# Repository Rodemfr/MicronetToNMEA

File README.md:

# MicronetToNMEA

## Note to Teensy users

MicronetToNMEA has migrated to ESP32. For Teensy-based hardware, please refer to the legacy code in the [`teensy`](https://github.com/Rodemfr/MicronetToNMEA/tree/teensy) branch.

## Description

MicronetToNMEA is an Arduino project that converts data from Raymarine's wireless Micronet network into standard NMEA0183 sentences, making it readily compatible with laptop or tablet navigation software. Additionally, it can transmit NMEA navigation data from your device back to the Micronet network.

Required hardware:
- A Raymarine/Tacktick master device (one with an ON/OFF button)
- An ESP32 WROOM DevKitC based board ([such as uPesy Wroom DevKit](https://www.upesy.fr/products/upesy-esp32-wroom-devkit-board))
- A CC1101 based board operating in the 868/915MHz range (ensure you order one with the appropriate 868MHz antenna, not the 433MHz one)

Optional components:
- A NMEA GPS/GNSS module connected via UART to provide position, time, date, SOG, and COG data to Micronet displays. The UBlox M8N is fully supported and can be configured directly by MicronetToNMEA
- A LSM303 compass module connected via I2C to provide magnetic heading data

Important Notice: While this DIY solution is an interesting project, please be aware that it may not withstand the harsh marine environment (salt, moisture, vibrations) as well as commercial equipment. MicronetToNMEA comes with no guarantees and should not be relied upon as your sole navigation system. For mission-critical applications, we recommend purchasing certified Raymarine/Tacktick equipment from authorized dealers.

## Authors & Contributors

* **Ronan Demoment** - [Rodemfr](https://github.com/Rodemfr) - Project creator and maintainer 
* **Dietmar Warning** - [dwarning](https://github.com/dwarning) - LSM303 Compass integration, bug fixes & testing
* **[j-lang](https://github.com/j-lang)** - UBLOX M8N initialization code & testing

## License

MicronetToNMEA is released under the GPLv3 license. See LICENSE.txt for complete details.

## Building the Project

The project can be built using [Visual Studio Code](https://code.visualstudio.com/) with the [PlatformIO](https://platformio.org/) extension installed.

For detailed instructions, please refer to the [User Manual](https://github.com/Rodemfr/MicronetToNMEA/blob/master/doc/user_manual/user_manual.md).

## Acknowledgments

* Special thanks to the YBW.com forum members who initiated the investigation of the Micronet protocol. Technical discussions can be found here: https://forums.ybw.com/index.php?threads/raymarines-micronet.539500/
* We appreciate all users who provide feedback and report issues, helping improve the software

## Hardware Setup

For the default WROOM DevKitC configuration, connect the CC1101 module as follows:

```
CC1101     WROOM DevKitC
SI     <-- Pin 23 (VSPI_MOSI)
SO     --> Pin 19 (VSPI_MISO)
SCK    <-- Pin 18 (VSPI_SCK)
CS     <-- Pin 5 (VSPI_CS)
GD0    --> Pin 35
GND    <-> GND
3.3V   <-- 3.3V
```

NMEA GNSS device connection (UART 2):

```
GNSS     WROOM DevKitC
TXD  --> Pin 16  (RX2)
RXD  <-- Pin 17  (TX2)
GND  <-> GND
3.3V <-- 3.3V
```

LSM303DLH(C) compass connection:

```
LSM303DLH(C)    WROOM DevKitC
SCL         <-- Pin 22  (I2C_SCL)
SDA         <-> Pin 21  (I2C_SDA)
GND         <-> GND
3.3V        <-- 3.3V
```

The system supports LSM303DLH, LSM303DLHC, and LSM303AGR compass modules, automatically detecting and configuring the appropriate driver.

To customize the pinout or use different hardware, modify the definitions in `BoardConfig.h`. See the [User Manual](https://github.com/Rodemfr/MicronetToNMEA/blob/master/doc/user_manual/user_manual.md) for configuration details.

## Quick Start Guide

1. Connect your ESP board via USB
2. Open a terminal (e.g., [Tera Term](http://www.teraterm.org/)) to access the configuration menu
3. Power up your Micronet network
4. Calibrate RF frequency (use "Calibrate RF frequency" menu and follow instructions)
5. Attach to the closest network (use "Attach to closest network" menu)
6. Start the NMEA conversion using "Start NMEA conversion"

Tips and Features:

- After initial setup, MicronetToNMEA automatically enters conversion mode on power-up
- Press ESC during conversion to access the configuration menu
- The system captures and applies network calibration values (wind speed, temperature, etc.)
- All settings (calibration, network ID) are stored in EEPROM
- Use "Scan surrounding Micronet traffic" to monitor network communications
- "Test RF quality" helps optimize converter placement for best signal reception

## Documentation

For comprehensive setup and configuration details, consult the [User Manual](https://github.com/Rodemfr/MicronetToNMEA/blob/master/doc/user_manual/user_manual.md) in the doc directory.

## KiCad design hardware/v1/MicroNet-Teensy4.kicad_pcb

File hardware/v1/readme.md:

### KICAD schematic and pcb
### STL for suitable case

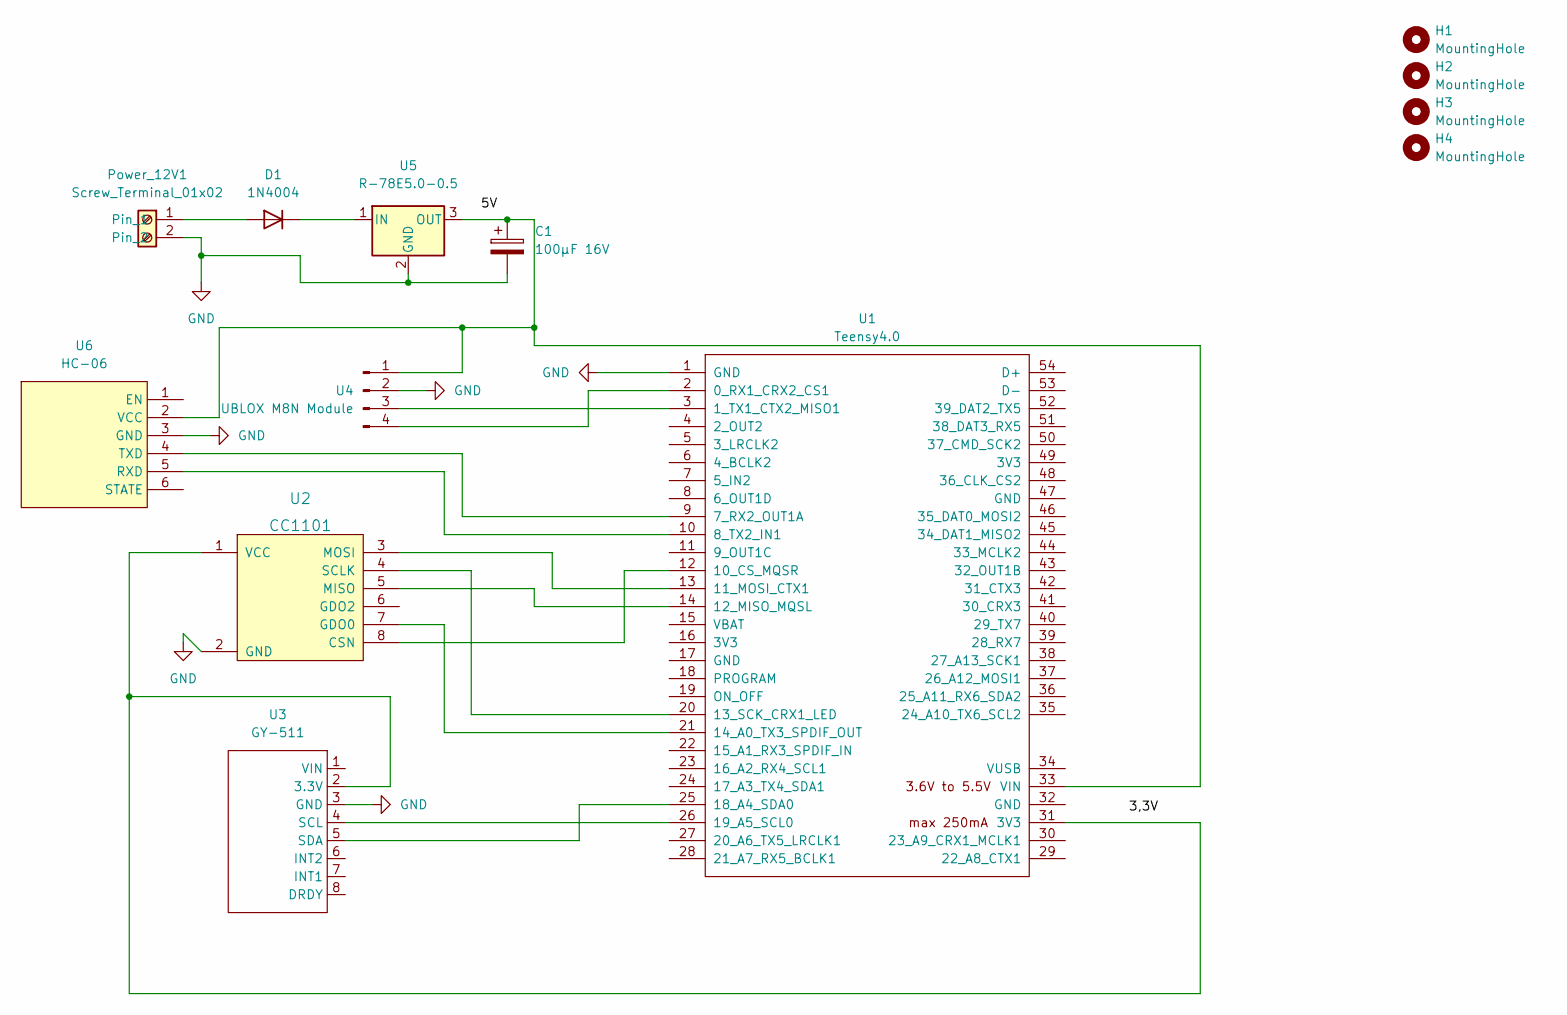
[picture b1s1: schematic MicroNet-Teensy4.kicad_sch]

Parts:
C1: 100µF 16V; CP_Radial_D6.3mm_P2.50mm
D1: 1N4004; D_DO-41_SOD81_P10.16mm_Horizontal
H1, H2, H3, H4: MountingHole; MountingHole_3.2mm_M3
Power_12V1: Screw_Terminal_01x02; PhoenixContact_MC_1,5_2-G-3.5_1x02_P3.50mm_Horizontal
U1: Teensy4.0; Teensy40
U2: CC1101
U3: GY-511
U4: UBLOX M8N Module; JST_XH_B4B-XH-A_1x04_P2.50mm_Vertical
U5: R-78E5.0-0.5; Converter_DCDC_RECOM_R-78E-0.5_THT
U6: HC-06

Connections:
GND: C1.2, Power_12V1.2, U1.1 (GND), U2.2 (GND), U3.3 (GND), U4.2, U5.2 (GND), U6.3 (GND); also elsewhere on the board
unnamed: C1.1, U1.33 (VIN), U4.1, U5.3 (OUT), U6.2 (VCC)
unnamed: D1.1 (K), U5.1 (IN)
unnamed 3: D1.2 (A), Power_12V1.1; also elsewhere on the board
unnamed: U1.2 (0_RX1_CRX2_CS1), U4.4
unnamed: U1.3 (1_TX1_CTX2_MISO1), U4.3
unnamed: U1.12 (10_CS_MQSR), U2.8 (CSN)
unnamed: U1.13 (11_MOSI_CTX1), U2.3 (MOSI)
unnamed: U1.14 (12_MISO_MQSL), U2.5 (MISO)
unnamed: U1.20 (13_SCK_CRX1_LED), U2.4 (SCLK)
unnamed: U1.21 (14_A0_TX3_SPDIF_OUT), U2.7 (GDO0)
unnamed: U1.25 (18_A4_SDA0), U3.5 (SDA)
unnamed: U1.26 (19_A5_SCL0), U3.4 (SCL)
unnamed: U1.31 (3V3), U2.1 (VCC), U3.2 (3.3V)
unnamed: U1.9 (7_RX2_OUT1A), U6.4 (TXD)
unnamed: U1.10 (8_TX2_IN1), U6.5 (RXD)

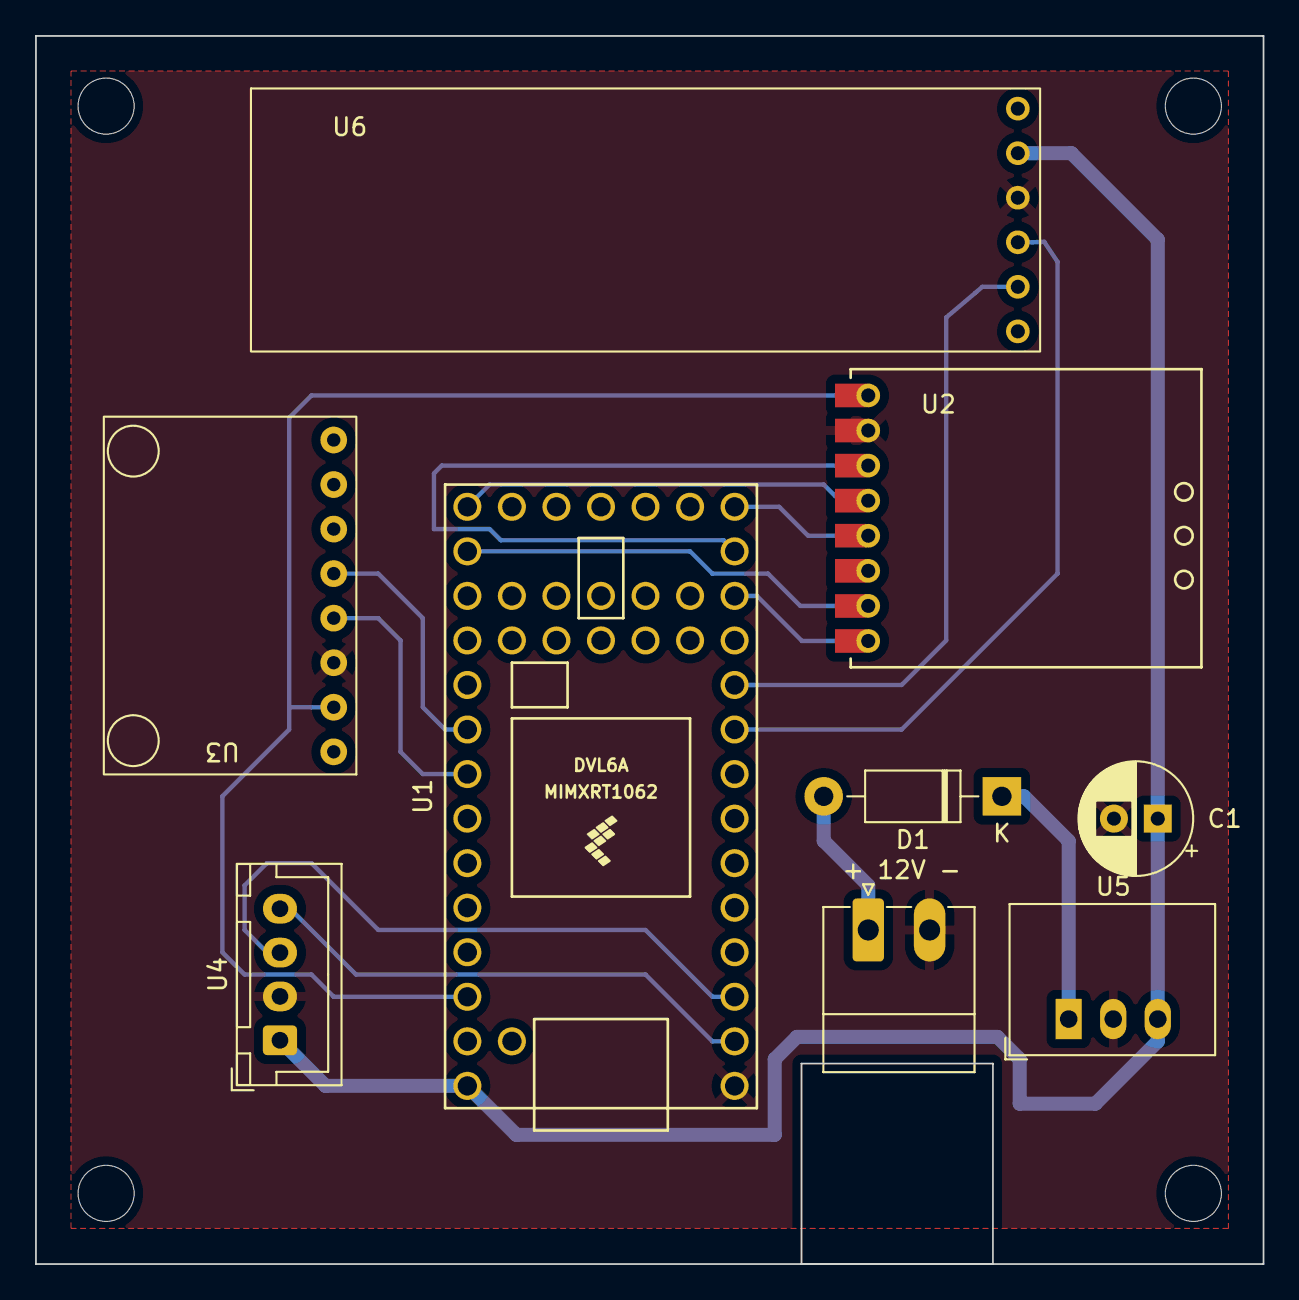
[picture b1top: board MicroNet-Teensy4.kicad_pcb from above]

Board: 2 copper layers, 70.0 x 70.0 mm, 13 parts (0 on the bottom side), 16 nets.

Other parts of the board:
+ 12V - : Screw_Terminal_01x02; PhoenixContact_MC_1,5_2-G-3.5_1x02_P3.50mm_Horizontal

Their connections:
GND: + 12V -.2; also elsewhere on the board
unnamed 3: + 12V -.1; also elsewhere on the board

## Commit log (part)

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2021-03-27 Send GNSS data to Micronet display
2021-03-27 Updated Tx slot calculation for a more robust version
2021-03-27 Add warning on the timing formula
2021-03-28 Fix slot time calculation
2021-04-01 Improve data management
2021-04-02 Use 0x03 command to get a synchronous transmission slot
2021-04-02 Minor fixes
2021-04-02 Optimize transmission routine
2021-04-03 Fix RF value in documentation
2021-04-03 Replace NMEA data structure by NavigationData structure
2021-04-03 Use scanf for NMEA position parsing
2021-04-03 Minor fix
2021-04-05 Handle variable slot size
2021-04-05 Clean-up code
2021-04-05 Remove useless debug stuff
2021-04-05 Close TODOs
2021-04-15 Fix COG/SOG bug
2021-05-20 Fix NMEA/CONSOLE mix bug when in conversion mode
2021-05-21 Fix bad usage of EEPROM
2021-05-24 Add a configuration define to disable NMEA checksum verification
2021-06-13 Use get & put methods to extend EEPROM/Flash lifecycle
2021-06-13 Fix EEPROM write bug
2021-06-27 Add LSM303DLH Driver for magnetic heading
2021-06-30 Add Magnetometer into configuration structure in EEPROM
2021-07-01 Fix GNSS latitude decoding bug
2021-07-04 Fix GGA sentence decoding bug
2021-07-04 Fix LSM303DLH register writing bug
2021-07-04 Quick & dirty fix of UART/RF disturbances
2021-07-26 Fix heading calculation bug
2021-07-26 Fix Micronet timing calculation bug
2021-07-31 Compass cleanup
2021-07-31 Disable heading feeding for now
2021-08-29 Add one digit to speed in NMEA conversion
2021-08-29 Use tty's latest Tx window definition
2021-08-29 Use tty's latest window definition (2)
2021-08-30 Improve Micronet message display in traffic scan mode
2021-09-03 Create a function to build network map from 0x01 message
2021-09-08 Remove useless iostream include to save memory
2021-09-10 Dynamically find LSM303 I2C adresses
2021-09-11 Add heading to Nav message
2021-09-11 Create pure virtual NavCompassDriver class
2021-09-12 Add Dietmar's LSM303DLHC code
2021-09-12 Fix LSM303DLH Code
2021-09-12 Take pitch angle into account in heading calculation
2021-09-12 Scale DLHC reading with axis coeeficients
2021-09-12 Add comments to LSM303DLHDriver
2021-09-18 Use USB console by default
2021-09-18 Add filtering to compass heading
2021-09-18 Revert bad calculations for DHLC
2021-09-18 Add eclipse's settings folder to gitignore
2021-09-18 Reduce filtering strength
2021-09-18 Use RF fifo threshold as interrupt source
2021-09-18 Create RfDriver class to collect Rf related code
2021-09-18 few corrections for LSM303DLHC
2021-09-18 Remove polling in RF ISR
2021-09-19 Prepare timer usage for RF transmission
2021-09-19 Use timer interrupt to trigger RF transmission
2021-09-20 Use setGDO0 instead of setGDO
2021-09-21 Use GDO0 interrupt for transmission callback
2021-09-21 Remove debug print
2021-09-21 Wait for end of serial initialization before start
2021-09-21 Use a single message to send data to display
2021-09-21 Fix parameter decoding bug
2021-09-22 Remove blocking calls during Serial init
2021-09-22 Remove reference to bluetooth
2021-09-24 ArduinoIDE is case sensitive for header files
2021-09-24 make the compass working for LSM303DHLC - preliminary
2021-09-26 Change LSM303DLH acceleration axis signs
2021-09-29 Add a menu for RF frequency analysis
2021-09-30 Remove some compilation warnings
2021-09-30 Update Micronet doc
2021-10-01 Update doc
2021-10-01 Reduce bandwidth when tuning frequency
2021-10-03 Fix frequency offset bug
2021-10-03 Clean-up frequency offset management
2021-11-28 Update frequency settings
2021-12-11 Update User Manual
2021-12-11 Update gitignore
2021-12-18 Add schematics to user manual
2021-12-18 Add Fritzing schematics
2021-12-20 Fix too long message issue
2022-01-03 Remove bad include of wiring.h
2022-01-03 Fix endTransmission bug
2022-01-03 Rename frequency parameters with correct unit
2022-01-04 Last name change MHz to KHz
2022-04-03 Correct RF baudrate by the same ratio than RF frequency
2022-04-29 Update MicronetToNMEA.ino
    Add initialization of ublox M8N GPS module
2022-04-29 Update BoardConfig.h
    Add initialization of ublox M8N GPS module
2022-05-05 Update MicronetCodec.cpp
    Fix too long message issue II: alternating messages for time&date and position data from gnss
2022-05-05 Update MicronetToNMEA.ino
    enable VTG for SOG & COG
2022-05-10 Remove useless correction of baudrate
2022-05-10 Fix baudrate scale error
2022-05-10 Make data fields configurable in sending API
2022-05-10 Use new data sending function
2022-05-11 Add baudrate calibration menu
2022-05-11 Fix compass filtering issue
2022-05-13 Remove baudrate search algorithm
2022-05-14 Update user manual figures
2022-05-14 Add magnetic heading to NMEA output
2022-05-18 Change NMEA maximum conversion rate
2022-05-22 Initial version of rewritten driver
2022-05-22 Non functional version
2022-05-31 Add CC1101 register debug function
2022-06-02 Change rewrite strategy
2022-06-12 Remove useless RF functions
2022-06-12 Continue clean-up
2022-06-19 Continue cleanup
2022-06-19 Update headers
2022-06-20 Remove useless code
2022-06-25 Enable multi message transmission
2022-06-26 Fix TX transition problem
2022-06-27 Fix Tx FIFO bug
2022-06-27 Allow pushing new transmits during transmission
2022-06-28 Fix timer reprog bug
2022-06-29 Don't use serial callback for GNSS
2022-06-29 Update Micronet spec
2022-06-29 Remove link between MnetSlaveDevice and RfDriver
2022-06-29 Add signal strength byte in encoded messages
2022-07-06 Add Device Info data field
2022-07-09 Fix bad RX FIFO handling in case of slow SPI
2022-07-09 read CC1101 FIFO by polling into ISR
2022-07-10 Continue SPI clean-up for Teensy 4.0
2022-07-10 Add temporary debug code
2022-07-10 Fix timing issues
2022-07-10 Transmit data through SPI polling instead of ISR
2022-07-10 Minor rewrite
2022-07-13 Update Micronet timings with latest measurements
2022-07-14 Use WFI instruction to reduce power consumption
2022-07-14 First attempt to solve crash issue
2022-07-14 Second fix for SW crash
2022-07-14 Add support for Node Info
2022-07-14 Fix preamble length in bytes
2022-07-14 Set charge level to max in Node Info
2022-07-15 Change IF to 200kHz
2022-07-17 Schedule CC1101's Low Power ON/OFF with TX timer
2022-07-17 Add 150us after power-down for XTAL restart time
2022-07-17 Use new Low Power functions
2022-07-17 Fix Teensy 4.0 issue
2022-07-17 Implement FREQ estimation algorithm
2022-07-17 Fix averaging sign bug
2022-07-18 Minor corrections
2022-07-20 Temporarily disable FREQEST algorithm
2022-07-21 Update M8NDriver.h
    Added initialization code for dynamic model: at sea
2022-07-21 Update M8NDriver.cpp
    Added initialization code for dynamic model: at sea
2022-07-23 Fix various small bugs
2022-07-24 Add support for NMEA battery level
2022-09-06 decode NMEA WMV sentences to micronet messages
2022-09-06 entry is anytime larger then 0
2022-09-08 Minor update
2022-09-10 Add RF quality test
2022-09-10 Use Ping to force displays to communicate during
2022-09-11 Remove PDF file from repo
2022-09-11 Reduce UM images size
2022-09-11 Add GNSS_SERIAL to sentence table
2022-09-11 Add title to configuration table
2022-09-11 Explicitely define char encoding
2022-09-16 Remove compilation warning
2022-09-18 Use DataBridge instead of NmeaDecoder/Encoder
2022-09-18 Fix NMEA decoding bugs
2022-09-18 Add support for external wind sensor
2022-09-19 Add support for DPT sentence
2022-09-21 Add support for VHW
2022-09-28 Add SCK connection to CC1101 schematic
2022-09-28 Resize image
2022-09-30 Add Remote Control commands to Micronet protocol
2022-10-01 Continue DataBridge implementation
2022-10-02 Add support for HDG decoding
2022-10-08 Fix various problems
2022-10-12 Add WP names
2022-10-12 WP name padding with spaces
2022-10-15 Fix wind repeating problem
2022-10-15 Add workaround for inverted RMB TO/FROM fields
2022-10-15 Disable OpenCPN 5.6.2 workaround by default
2022-10-15 Minor improvements on WP names
2022-10-16 Minor change
2022-10-16 Fix WP name table
2022-10-25 Fix wind repeating bug
2022-10-31 Rename XDG to XDR and VMC to VMGWP
2022-10-31 Make wind repeat feature configurable
2022-10-31 Quick fix
2022-11-01 Fix NMEA forwarding bug
2022-11-02 Avoid long polling in GDO0 ISR
2022-11-03 Reduce TX latency
2022-11-03 Reintroduce RF frequency tracking
2022-11-04 Use SPI Burst transfer to speedup ISR
2022-11-04 Fix Teensy 3.5/3.6 IRQ issue
2022-11-05 Fix cppcheck warnings
2022-11-05 Fix remaining ccpcheck warnings
2022-11-05 Disable frequency tracking
2022-11-05 Fix Arduino IDE warnings
2022-11-05 Re-enable frequency tracking
2022-11-05 Remove usage of FREQOFF in frequency configuration
2022-11-05 Remove freq maps
2022-11-05 Disable PLL auto calibration
2022-11-06 Don't apply limiter for FREQOFF value
2022-11-06 Avoid device repetition in RF quality test
2022-11-06 Move all code to src subfolder
2022-11-06 Ignore sloeber folder
2022-11-06 Remove some more warnings
2022-11-06 Fix ccpcheck warnings
2022-11-06 Clean-up CC1101Driver
2022-11-07 Add comments
2022-11-08 Comment CC1101Driver code
2022-11-08 Fix FW version inversion
2022-11-08 Beautifuling...
2022-11-09 Automatically handle multiple slaves
2022-11-11 Fix console issue
2022-11-11 Revert bad BoardConfig.h
2022-11-11 Fix BoardConfig.h
2022-11-11 Fix buffer overflow bug
2022-11-11 Disable frequency tracking when not necessary
2022-11-11 Update version
2022-11-11 Update user manual and readme
2022-11-12 Reduce SPI delays for read accesses
2022-11-12 Fix heading & waterspeed handling
2022-11-14 Fix handling of magnetic heading
2022-11-15 fix issue #50 HDG info not sent to Micronet
2022-11-16 Hardware files
    PCB and STL
2022-11-16 Increase SpiStrobe CS delay
2022-12-02 Fix wrong heading offset handling
2022-12-02 Apply scal factors to DLHC magnetic readings
2022-12-02 Add heading offset and magvar to info menu
2022-12-02 Other heading related fixes
2022-12-02 Fix bad heading handling
2022-12-03 Add information on EEPROM config
2022-12-04 Remove magvar from mag heading value
2022-12-07 Fix wrong HDG syntax
2022-12-07 Remove debug code
2022-12-10 Fix tilt calculation error
2022-12-10 Reduce heading filtering strengh
2022-12-12 Fix DPT sentence
2022-12-12 Fix repetition of VHW sentence
2022-12-14 Fix VHW sentence
2022-12-14 Add missing calibration info in menu 1
2022-12-15 Make heading axis configurable
2023-02-04 Create vscode/PIO project
2023-02-06 Format code with clang-format
2023-02-06 Change .gitignore for vscode/pio
2023-02-07 Fix default configuration
2023-02-07 Remove vscode directory
2023-03-01 Add SPD emulation
2023-03-02 Fix SPD emulation
2023-03-03 Update release note
2023-03-04 Reorganize code
2023-03-04 Disable SPD emulation by default
2023-04-10 Update Micronet doc with alarm commands
2023-06-11 Add compilation warning
2023-06-11 Use latest TeensyTimerTool
2023-06-24 Add GLL support
2023-06-25 Update documentation
2023-06-25 Fix warning
2024-01-01 Decode SOG & COG from RMC sentence
2024-03-17 Add COG/SOG filtering
2024-03-18 Update doc & version
2024-11-09 Add HW v2 3d file
2024-11-09 SW support for HW 2
2024-11-11 Compensate RF Tx delay
2024-11-12 Rename config constants
2025-01-05 Simplify v2 HW
2025-01-05 Minor updates
2025-01-12 Add BMP-580 & BT module
2025-01-12 Fix 3D case issues
2025-01-15 Add roll angle calculation
2025-01-18 Update HW
2025-01-18 Fix spelling
2025-01-29 Remove BMP-580 from HW
2025-02-02 Clean-up PCB
2025-02-02 I/O Renaming
2025-02-12 Improve heading robustness
2025-02-24 Update 3D Box code
2025-02-24 Various fixes for HW v2
2025-03-12 Add BT name configuration
2025-03-12 Fix BT conf bug
2025-03-12 Improve COG/SOG filter
2025-03-23 Add configuration menu
2025-03-25 Fix COG filter strength error
2025-11-05 First implementation of ESP32 version
2025-11-08 Enable Bluetooth
2025-11-08 Fix NMEA_IN Serial config
2025-11-08 Fix GNSS UART handling
2025-11-09 Add hardware v3
2025-11-09 Clean-up M8NDriver
2025-11-09 Comment code with AI
2025-11-11 Initial version of v3 HW
2025-11-15 Fix depth offset error
2025-11-27 Add first unit tests
2025-12-02 add tests and improve code
2025-12-26 Master test code
2025-12-26 Minor fixes to ESP32 HW
2025-12-26 Add Compass device
2025-12-26 Change default IO config
2025-12-26 Revert PWR supply polarity
2026-04-21 Remove Native env
2026-06-24 Minor compass related fixes
2026-06-24 Update HW to v3
